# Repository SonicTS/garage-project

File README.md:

# blaulicht-garage-proxy (MQTT)

A DIY setup that routes the HTTPS traffic of one Android app ("Blaulicht") through a self-hosted mitmproxy. When a specific flow pattern is detected, the mitmproxy addon publishes an MQTT command to a local Mosquitto broker (TLS + auth). An ESP8266 subscribed to that topic pulses a relay to open the garage.

This repo includes: Android per-app VPN client, a mitmproxy addon with MQTT publishing, ESP8266 RTOS-based firmware with MQTT over TLS, and infrastructure templates (systemd, firewall, MQTT broker hardening). Intended for experimentation and learning.

## Data flow (MQTT)

```
[Blaulicht app]
      |
      v
Android per-app VPN (VpnService + tun2socks) → SOCKS5 → mitmproxy --(MQTT/TLS publish)--> Mosquitto → ESP8266 → relay
      ^                                 TLS intercept (trusted CA)                 ^ TLS + auth            (garage door)
```

## Components

- Android per-app VPN client
  - VpnService-based app that forwards only the target app’s traffic via a SOCKS5 proxy (mitmproxy) using a tun2socks AAR.
- mitmproxy addon
  - Detects the flow trigger and publishes `open` to `garage/cmd` over TLS to Mosquitto on 8883.
  - Configurable via environment variables (`MQTT_HOST`, `MQTT_USER/PASS`, `TRIGGER_*`). See `infra/systemd/mitmproxy.service`.
- Mosquitto broker
  - TLS 1.2+, per-user passwords in `/etc/mosquitto/passwd`, and minimal permissions. See `docs/setup-mqtt-broker.md`.
- ESP8266 firmware
  - Connects to Wi‑Fi and MQTT over TLS, subscribes to `garage/cmd`, and publishes `garage/status`. Embed the CA in `lib/mqtt/src/mqtt.c`.

## Quickstart

1) Server (Ubuntu)
- Install Mosquitto and set up TLS + users: `docs/setup-mqtt-broker.md`.
- Deploy mitmproxy addon and set MQTT env: `docs/setup-server-ubuntu.md`.

2) Android
- Build and install the per-app VPN client (Android Studio). Point it to the server’s SOCKS5 port. Install the mitmproxy CA on the device.

3) ESP8266
- Open `esp8266/Garage-Controller` in PlatformIO. Set Wi‑Fi + MQTT config (including CA). Build and flash.

Security note: Use strong per-client credentials. Keep the broker LAN-only or restricted. Self-signed CA is fine for local deployments; keep the private key secure.

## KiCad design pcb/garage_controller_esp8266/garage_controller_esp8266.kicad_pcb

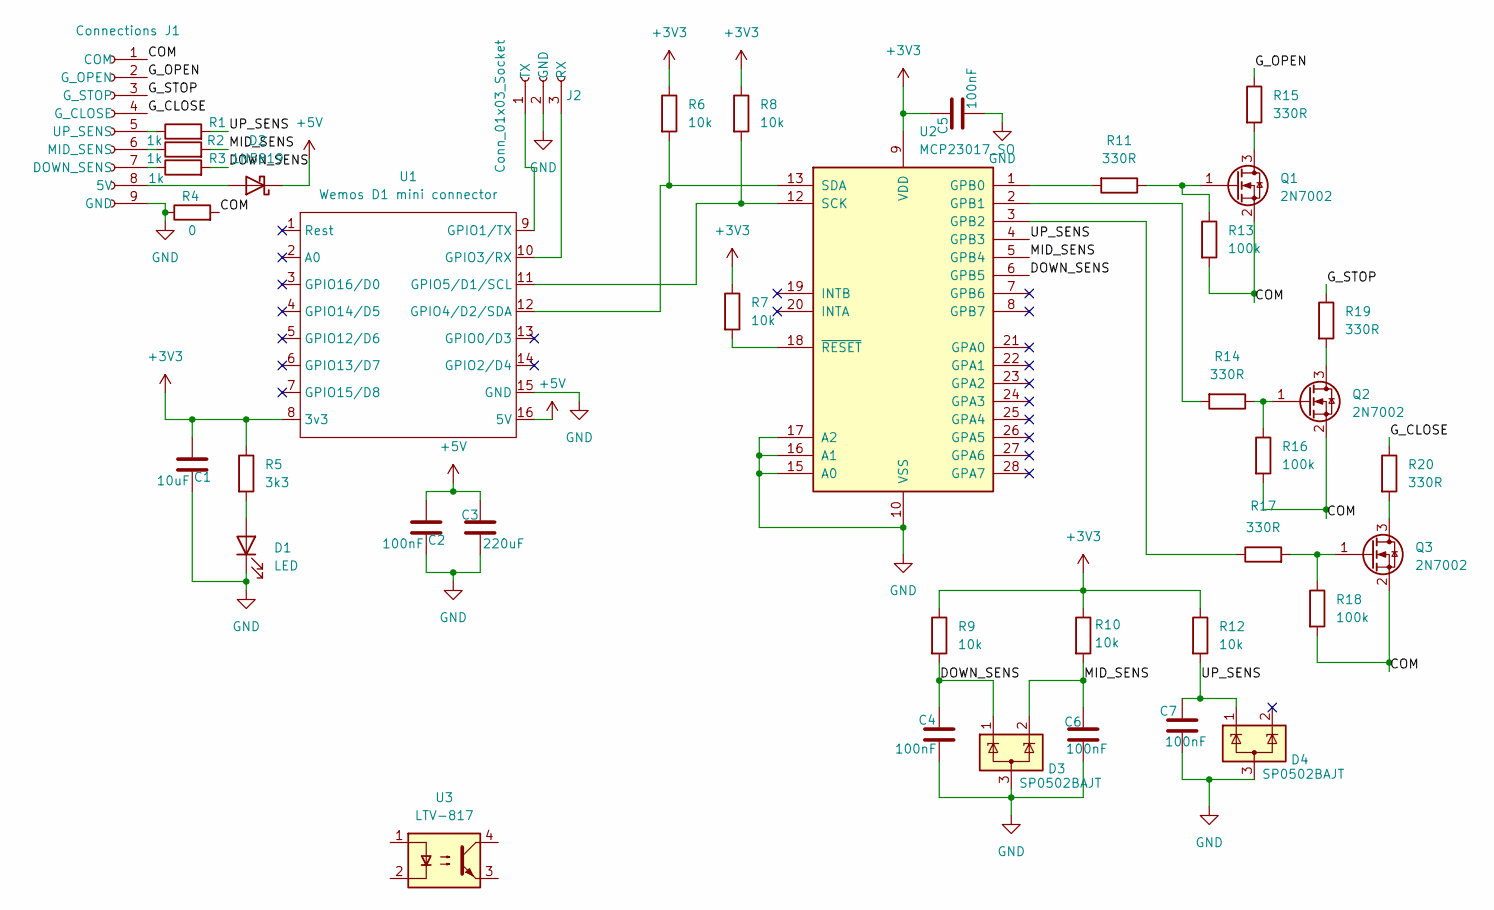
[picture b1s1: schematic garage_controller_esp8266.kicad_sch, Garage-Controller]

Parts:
C1: 10uF; C_0805_2012Metric_Pad1.18x1.45mm_HandSolder
C2, C4, C5, C6, C7: 100nF; C_0805_2012Metric_Pad1.18x1.45mm_HandSolder
C3: 220uF; CP_Elec_10x12.5
D1: LED; LED_0805_2012Metric_Pad1.15x1.40mm_HandSolder
D2: 1N5819; D_SOD-123
D3, D4: SP0502BAJT; SOT-323_SC-70
J1: Connections; PinSocket_1x09_P2.54mm_Vertical
J2: Conn_01x03_Socket; PinSocket_1x03_P2.54mm_Vertical
Q1, Q2, Q3: 2N7002; SOT-23
R1, R2, R3: 1k; R_0805_2012Metric_Pad1.20x1.40mm_HandSolder
R4: 0; R_0805_2012Metric_Pad1.20x1.40mm_HandSolder
R5: 3k3; R_1206_3216Metric_Pad1.30x1.75mm_HandSolder
R6, R7, R8, R9, R10, R12: 10k; R_0805_2012Metric_Pad1.20x1.40mm_HandSolder
R11, R14, R15, R17, R19, R20: 330R; R_0805_2012Metric_Pad1.20x1.40mm_HandSolder
R13, R16, R18: 100k; R_0805_2012Metric_Pad1.20x1.40mm_HandSolder
U1: Wemos D1 mini connector; Wemos D1 mini connectort
U2: MCP23017_SO; SOIC-28W_7.5x17.9mm_P1.27mm
U3: LTV-817; DIP-4_W7.62mm

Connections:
+3V3: C1.2, C5.1, R5.1, R6.1, R7.1, R8.1, R9.1, R10.1, R12.1, U1.8 (3v3), U2.9 (VDD)
+5V: C2.2, C3.1, D2.1 (K), U1.16 (5V)
/COM: J1.1 (COM), Q1.2 (S), Q2.2 (S), Q3.2 (S), R4.2, R13.2, R16.2, R18.2
/DOWN_SENS: C4.1, D3.1 (K), R3.2, R9.2, U2.6 (GPB5)
/G_CLOSE: J1.4 (G_CLOSE), R20.1
/G_OPEN: J1.2 (G_OPEN), R15.1
/G_STOP: J1.3 (G_STOP), R19.1
/MID_SENS: C6.1, D3.2 (K), R2.2, R10.2, U2.5 (GPB4)
/UP_SENS: C7.1, D4.1 (K), R1.2, R12.2, U2.4 (GPB3)
GND: C1.1, C2.1, C3.2, C4.2, C5.2, C6.2, C7.2, D1.1 (K), D3.3 (A), D4.3 (A), J1.9 (GND), J2.2 (GND), R4.1, U1.15 (GND), U2.10 (VSS), U2.15 (A0), U2.16 (A1), U2.17 (A2)
unnamed: D1.2 (A), R5.2
unnamed: D2.2 (A), J1.8 (5V)
unnamed: J1.7 (DOWN_SENS), R3.1
unnamed: J1.6 (MID_SENS), R2.1
unnamed: J1.5 (UP_SENS), R1.1
unnamed: J2.3 (RX), U1.10 (GPIO3/RX)
unnamed: J2.1 (TX), U1.9 (GPIO1/TX)
unnamed: Q1.3 (D), R15.2
unnamed: Q1.1 (G), R11.1, R13.1
unnamed: Q2.3 (D), R19.2
unnamed: Q2.1 (G), R14.1, R16.1
unnamed: Q3.3 (D), R20.2
unnamed: Q3.1 (G), R17.2, R18.1
unnamed: R6.2, U1.12 (GPIO4/D2/SDA), U2.13 (SDA)
unnamed: R8.2, U1.11 (GPIO5/D1/SCL), U2.12 (SCK)
unnamed: R11.2, U2.1 (GPB0)
unnamed: R14.2, U2.2 (GPB1)
unnamed: R17.1, U2.3 (GPB2)
unnamed: R7.2, U2.18 (~RESET)

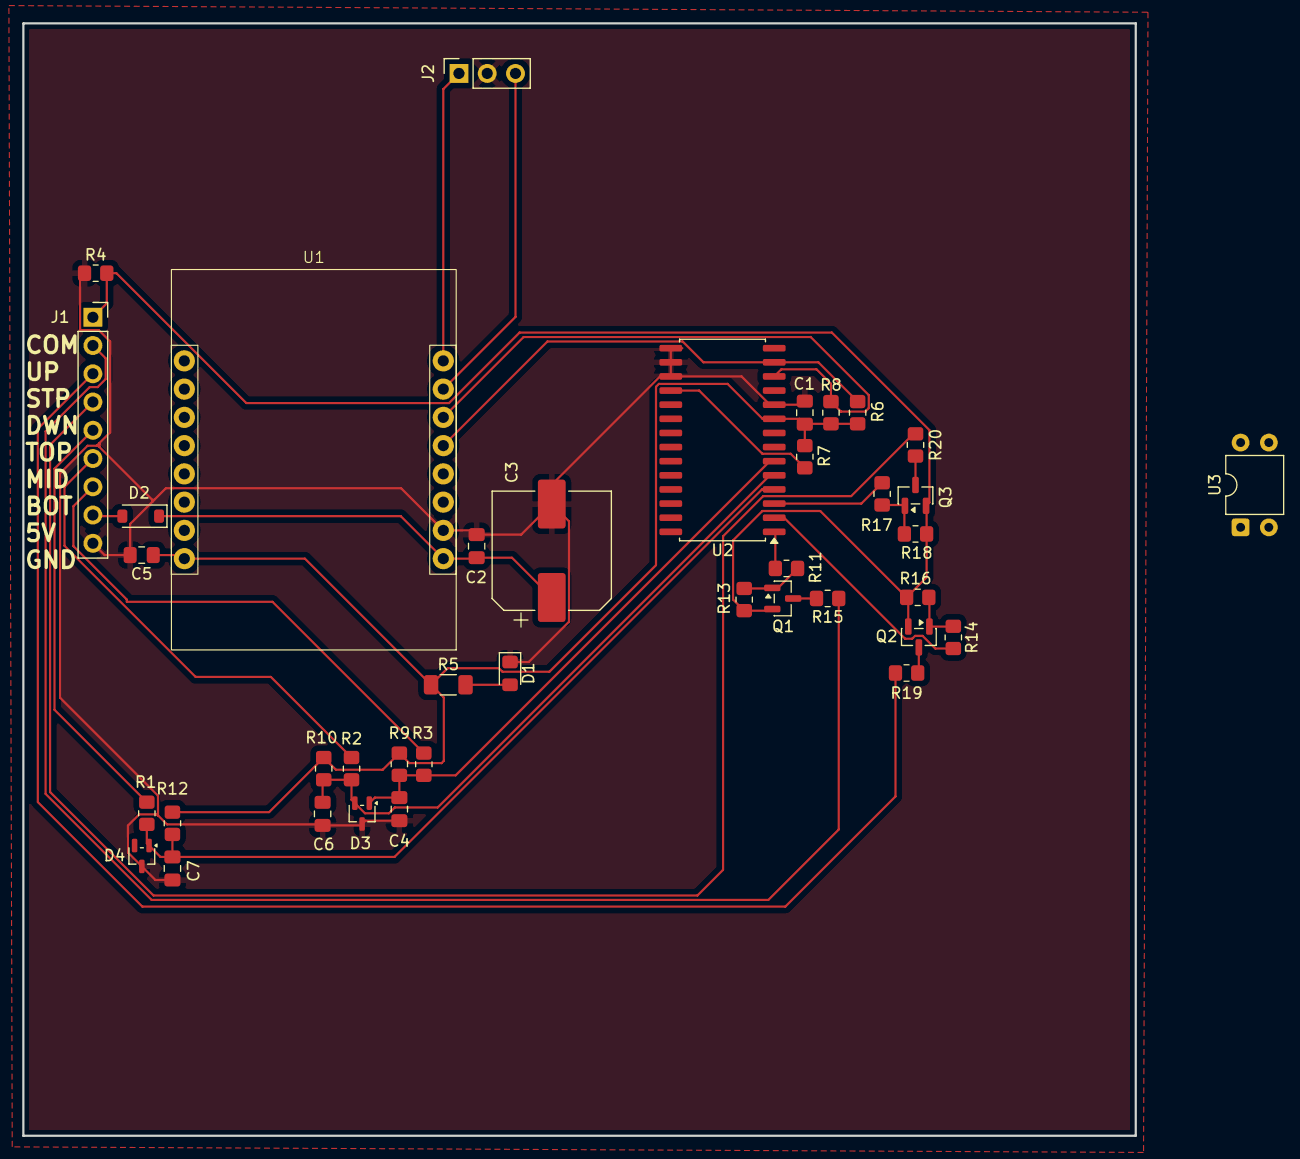
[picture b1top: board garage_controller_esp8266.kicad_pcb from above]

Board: 2 copper layers, 100.0 x 100.0 mm, 39 parts (0 on the bottom side), 29 nets.

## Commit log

2025-11-09 mitmproxy logs now
2025-11-09 Changed port
2025-11-09 Fixed mitmproxy logging
2025-11-09 Created apk
2025-11-12 Added --set block_global=false and imrpoved vpn app
2025-11-12 Improved vpn app
2025-11-16 Added first esp8266 working firmware with wifi service interface
2025-11-18 Created modules for their own responsibilities and started with wifi_manager, config_store, service_interface and mqtt-client
2025-11-18 Changed docs and setup files from http /trigger endpoint to mqtt system
2025-11-18 Update gitignore
2025-12-07 Added setup for mqtt broker
2025-12-07 Improved esp firmware
2025-12-08 Updated git ignore
2025-12-08 Added comments
2025-12-08 Added mqtt tls flutter app
2025-12-08 Added lib to the repo
2026-01-04 Imrpoved wifi connection reliability and disabled the pull up for the button pins
2026-01-31 added kicad stuff
2026-02-07 Started with box design
2026-03-14 Worked on the Box
2026-03-15 Added mcp23017
2026-03-20 Added uart
2026-03-21 Added gpio inversion config
2026-03-22 Added interactive BOM
2026-04-01 COntinued on box + clipper
2026-04-01 Improved spriung
2026-05-09 Changed pins for buttons and added clipper
2026-05-09 Wifi password are getting now correctly parsed
2026-05-09 Improved clipper and added compartment for relay pcb
2026-05-13 Improved top part
2026-05-14 Changed pins back
2026-05-24 Changed uart speed
2026-06-15 Improved wifi manager

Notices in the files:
pcb/garage_controller_esp8266/garage_controller_esp8266.kicad_pcb:
License: CC BY 4.0
pcb/garage_controller_esp8266/garage_controller_esp8266.kicad_sch:
creativecommons.org/licenses/by/4.0
